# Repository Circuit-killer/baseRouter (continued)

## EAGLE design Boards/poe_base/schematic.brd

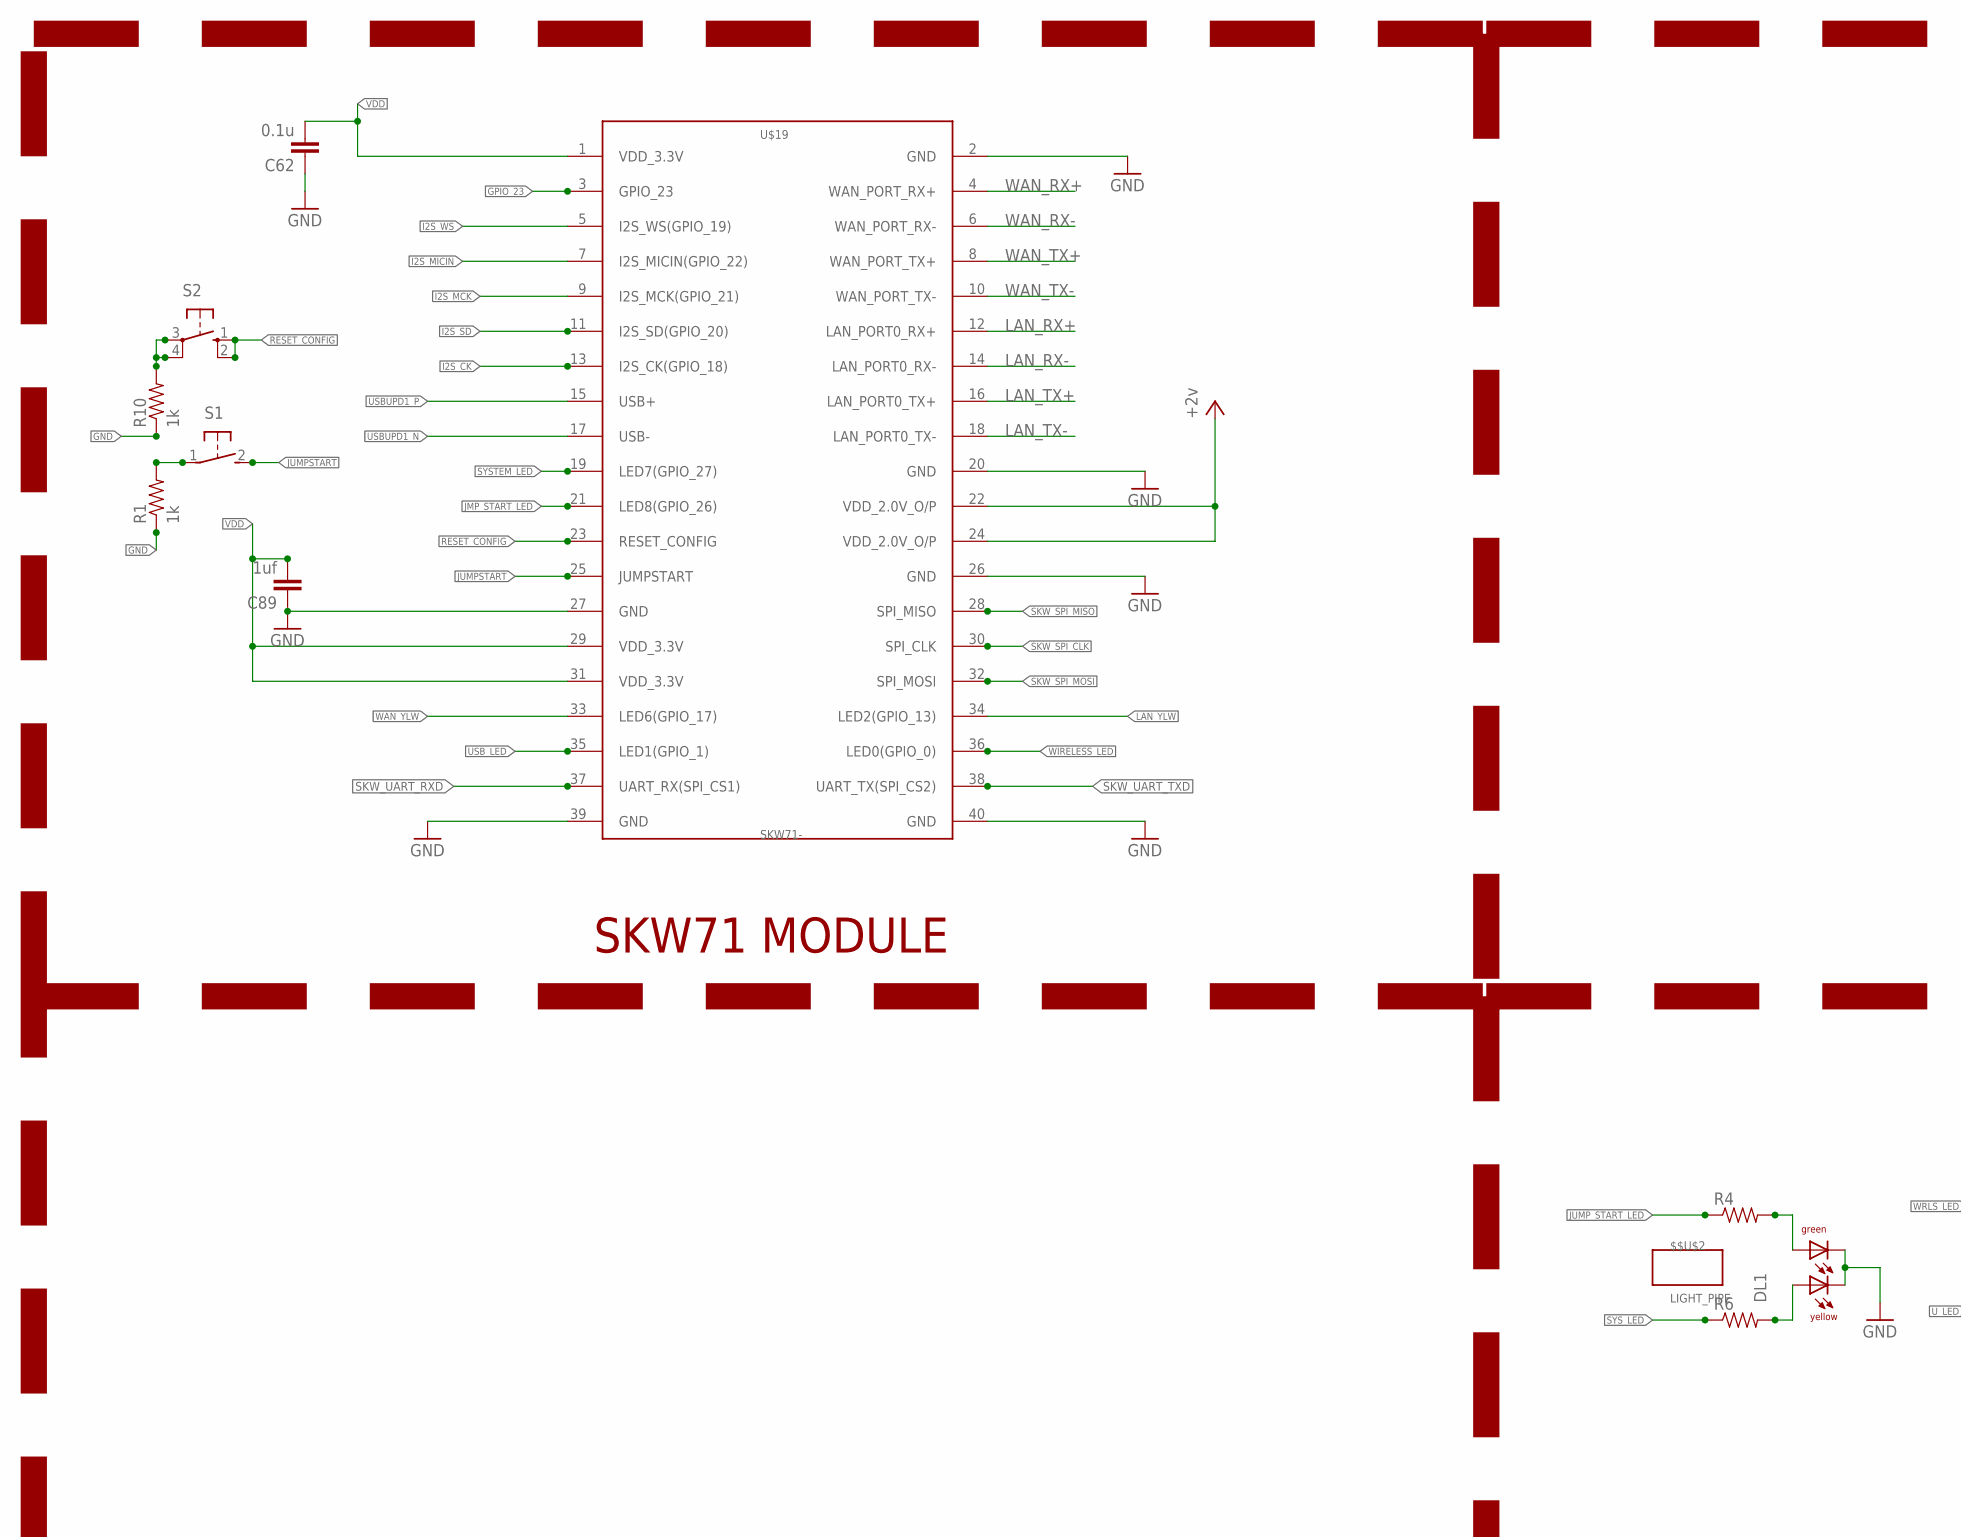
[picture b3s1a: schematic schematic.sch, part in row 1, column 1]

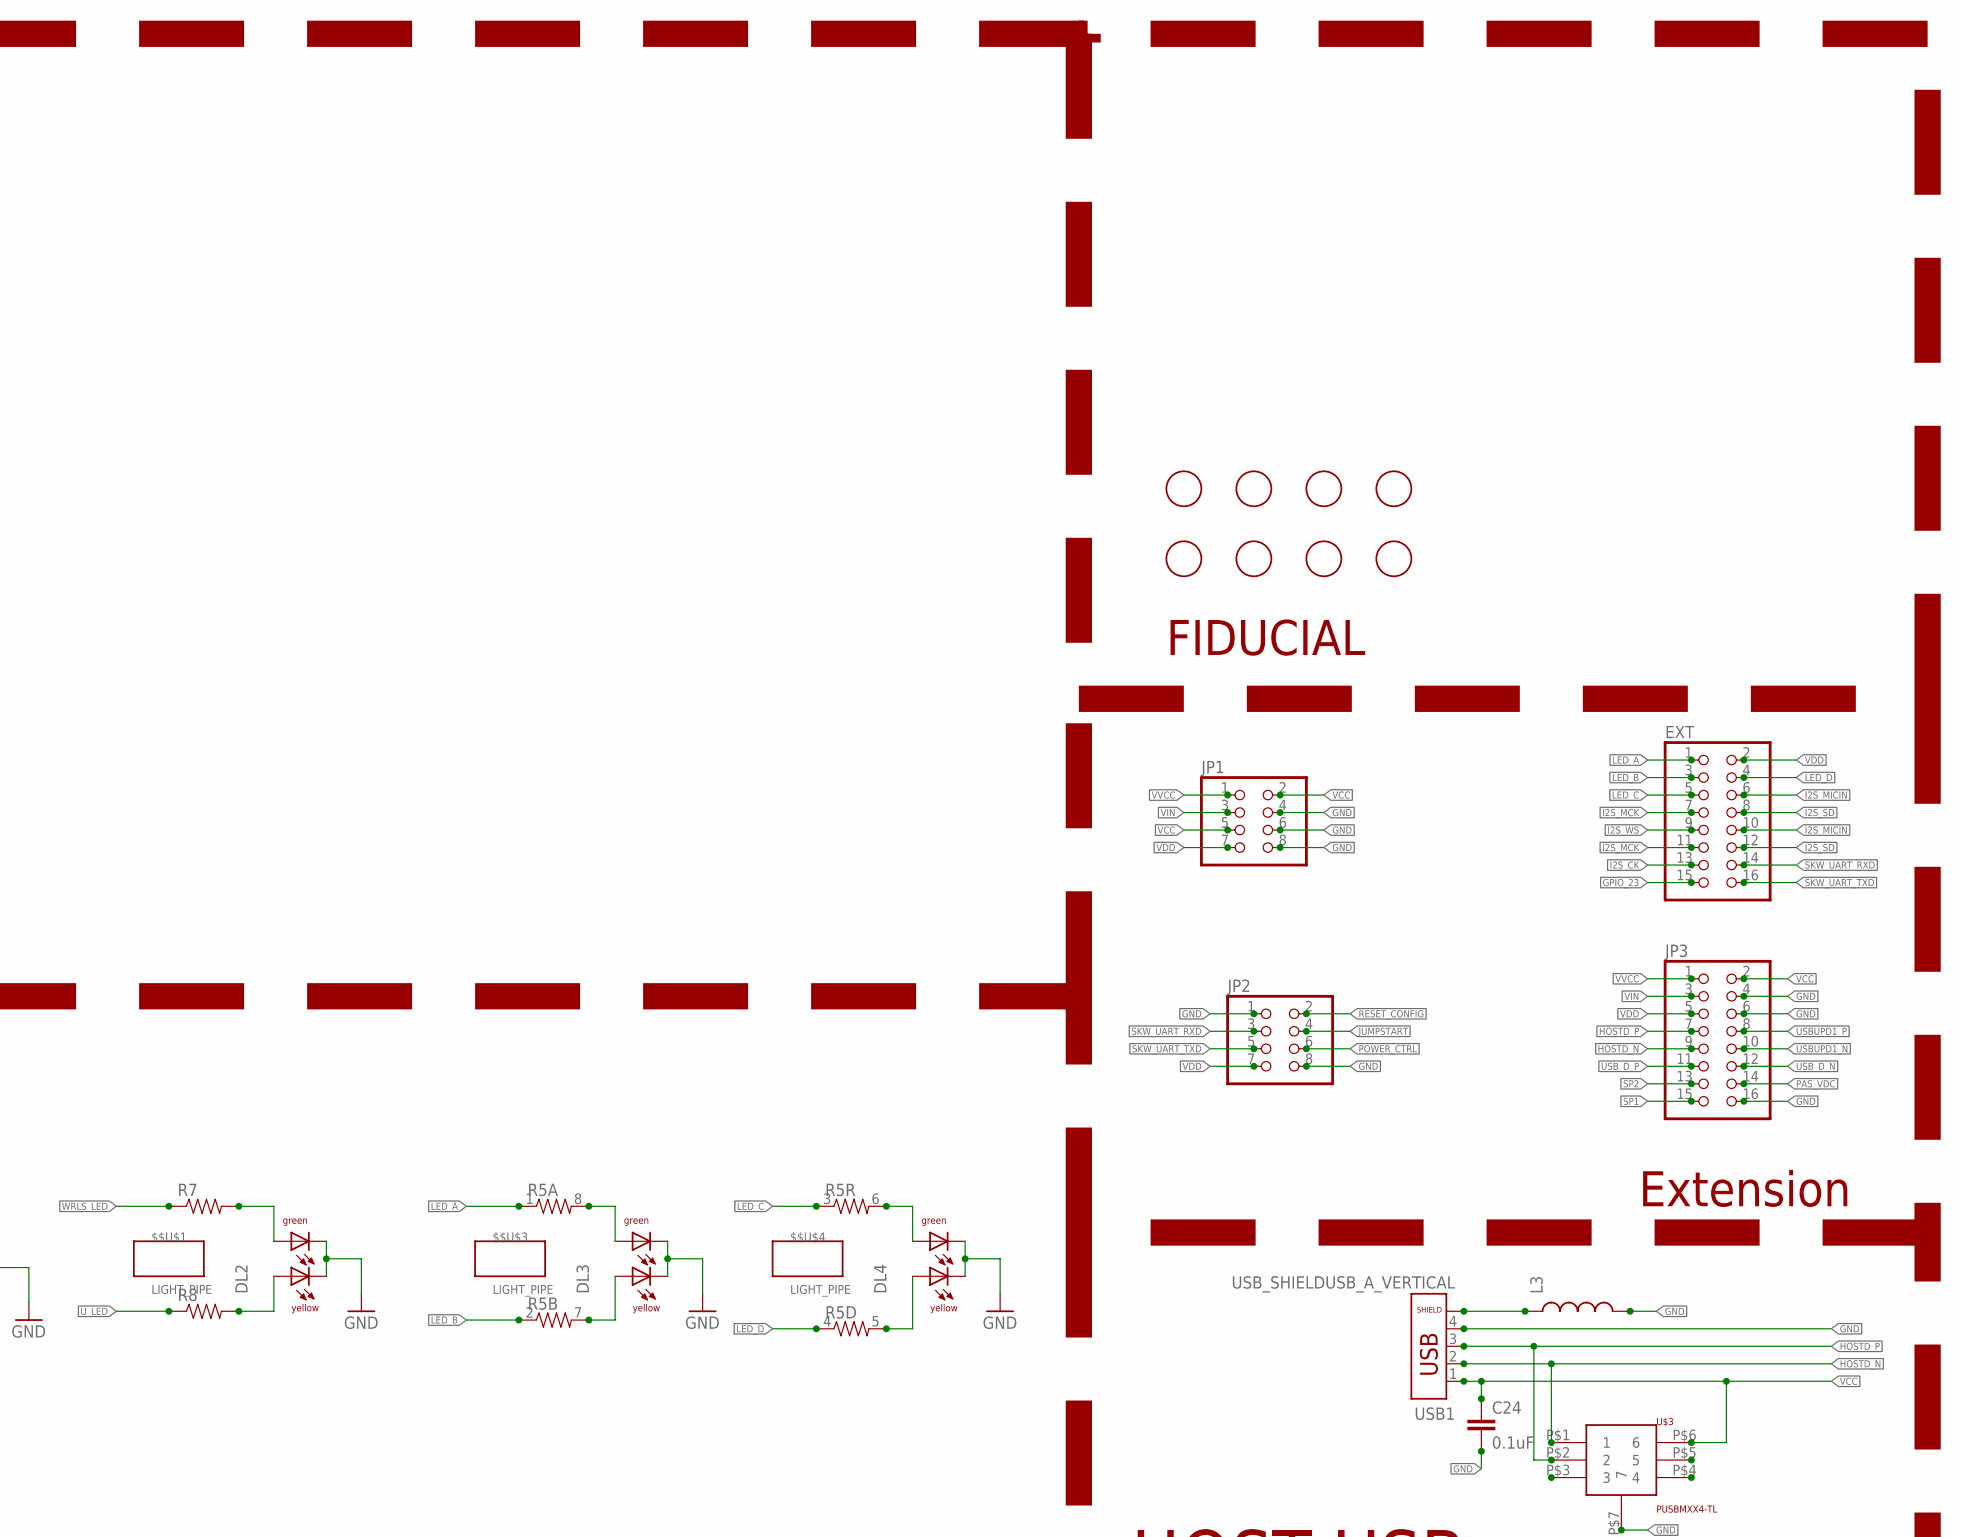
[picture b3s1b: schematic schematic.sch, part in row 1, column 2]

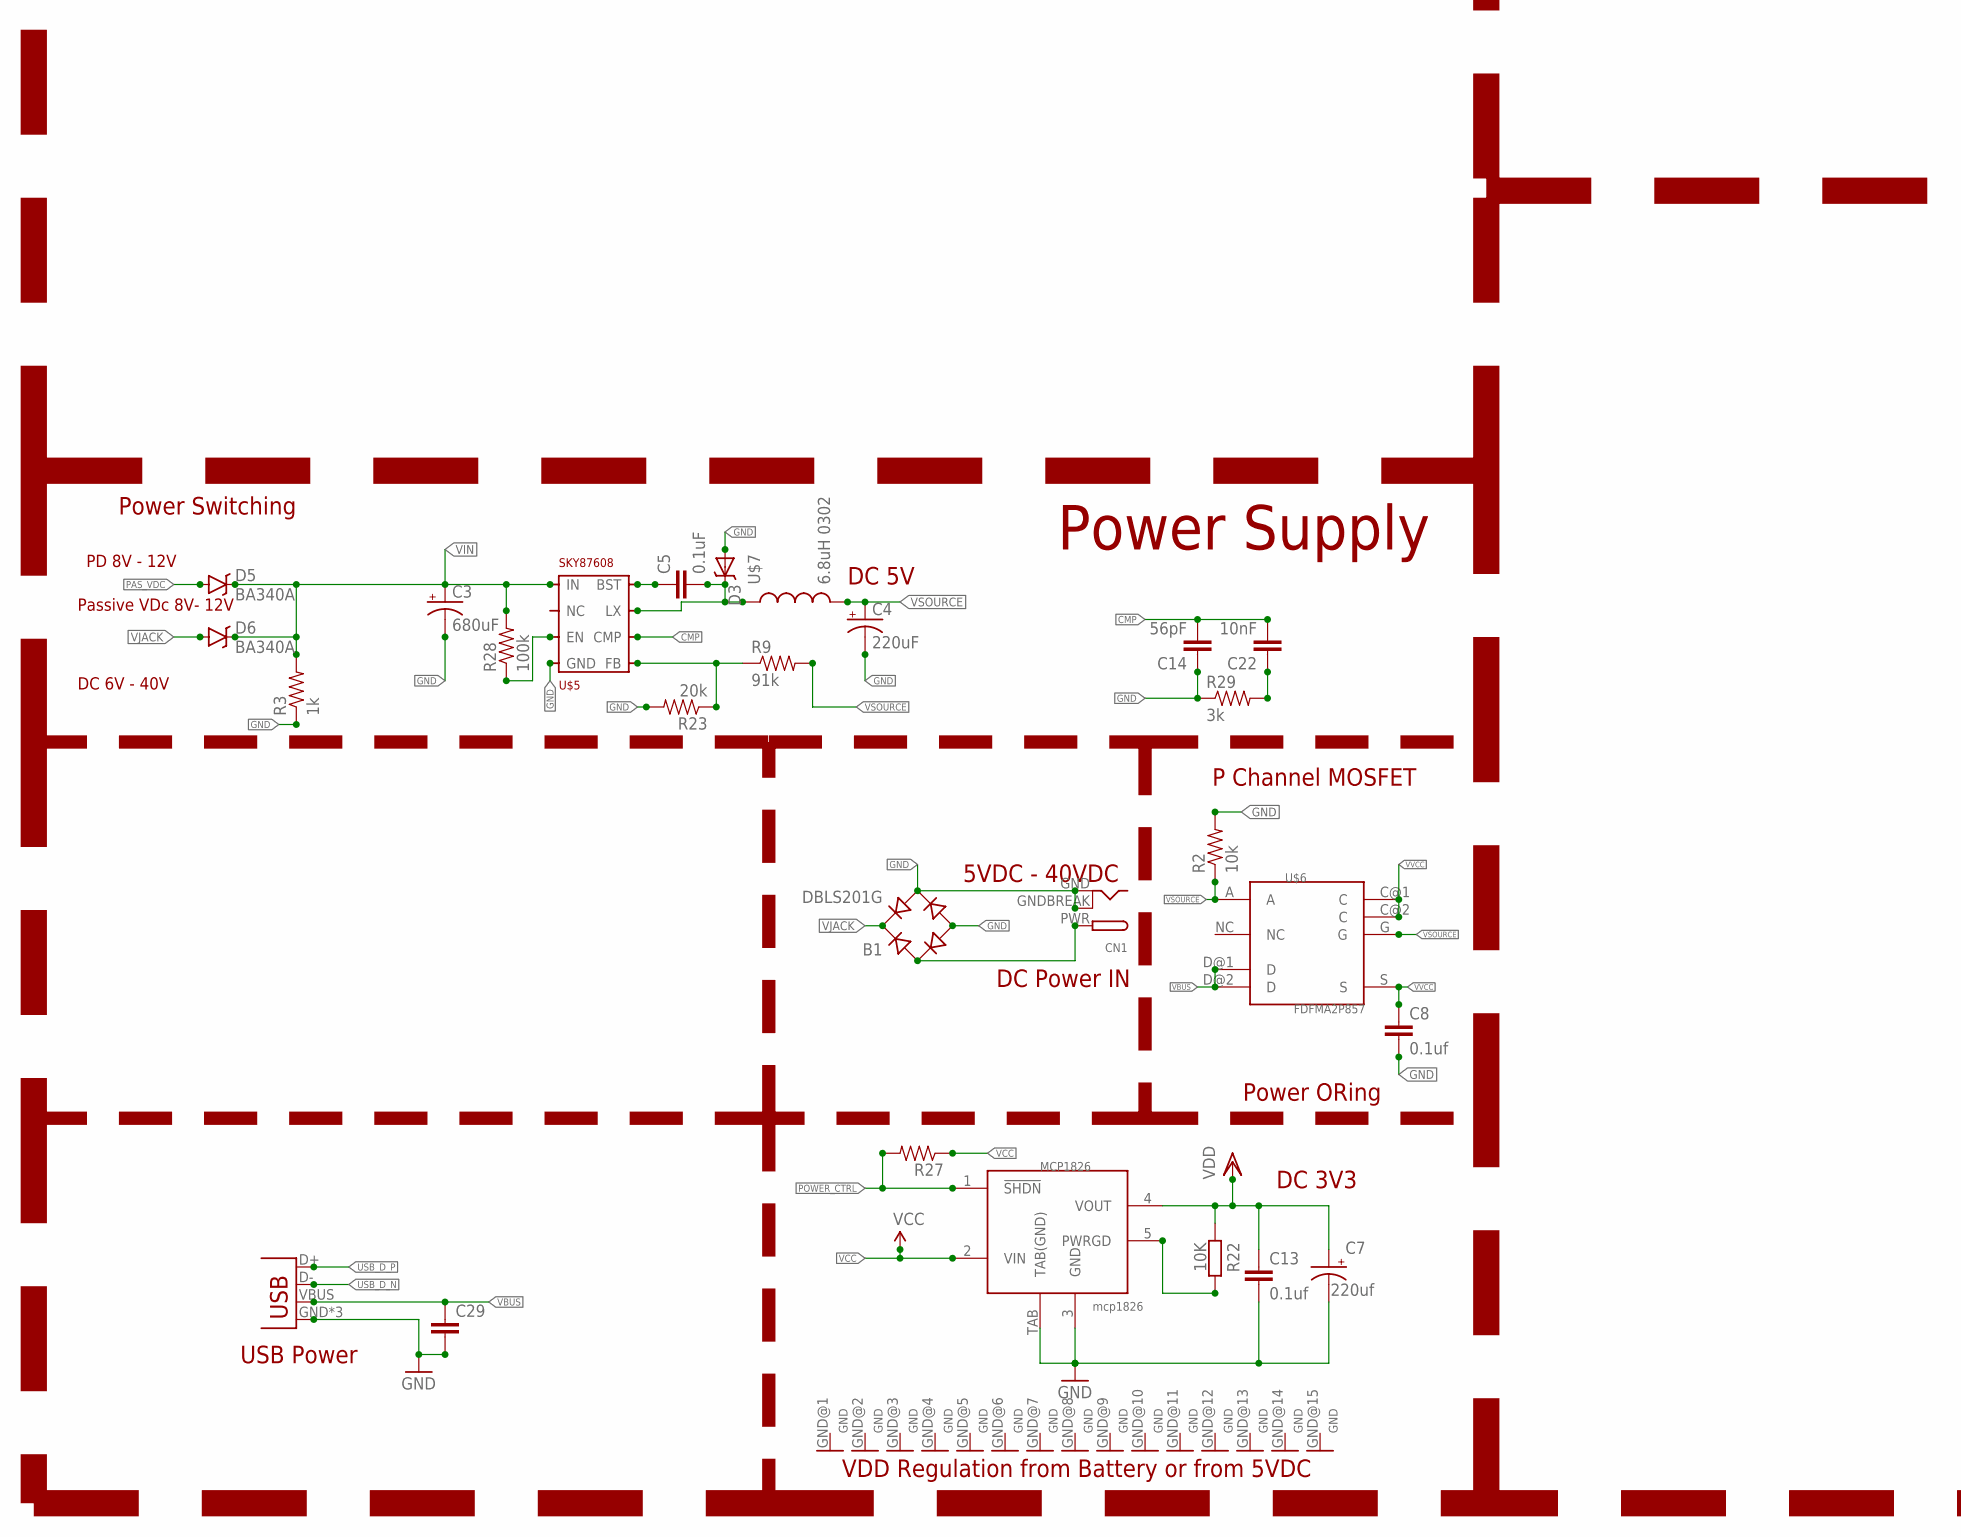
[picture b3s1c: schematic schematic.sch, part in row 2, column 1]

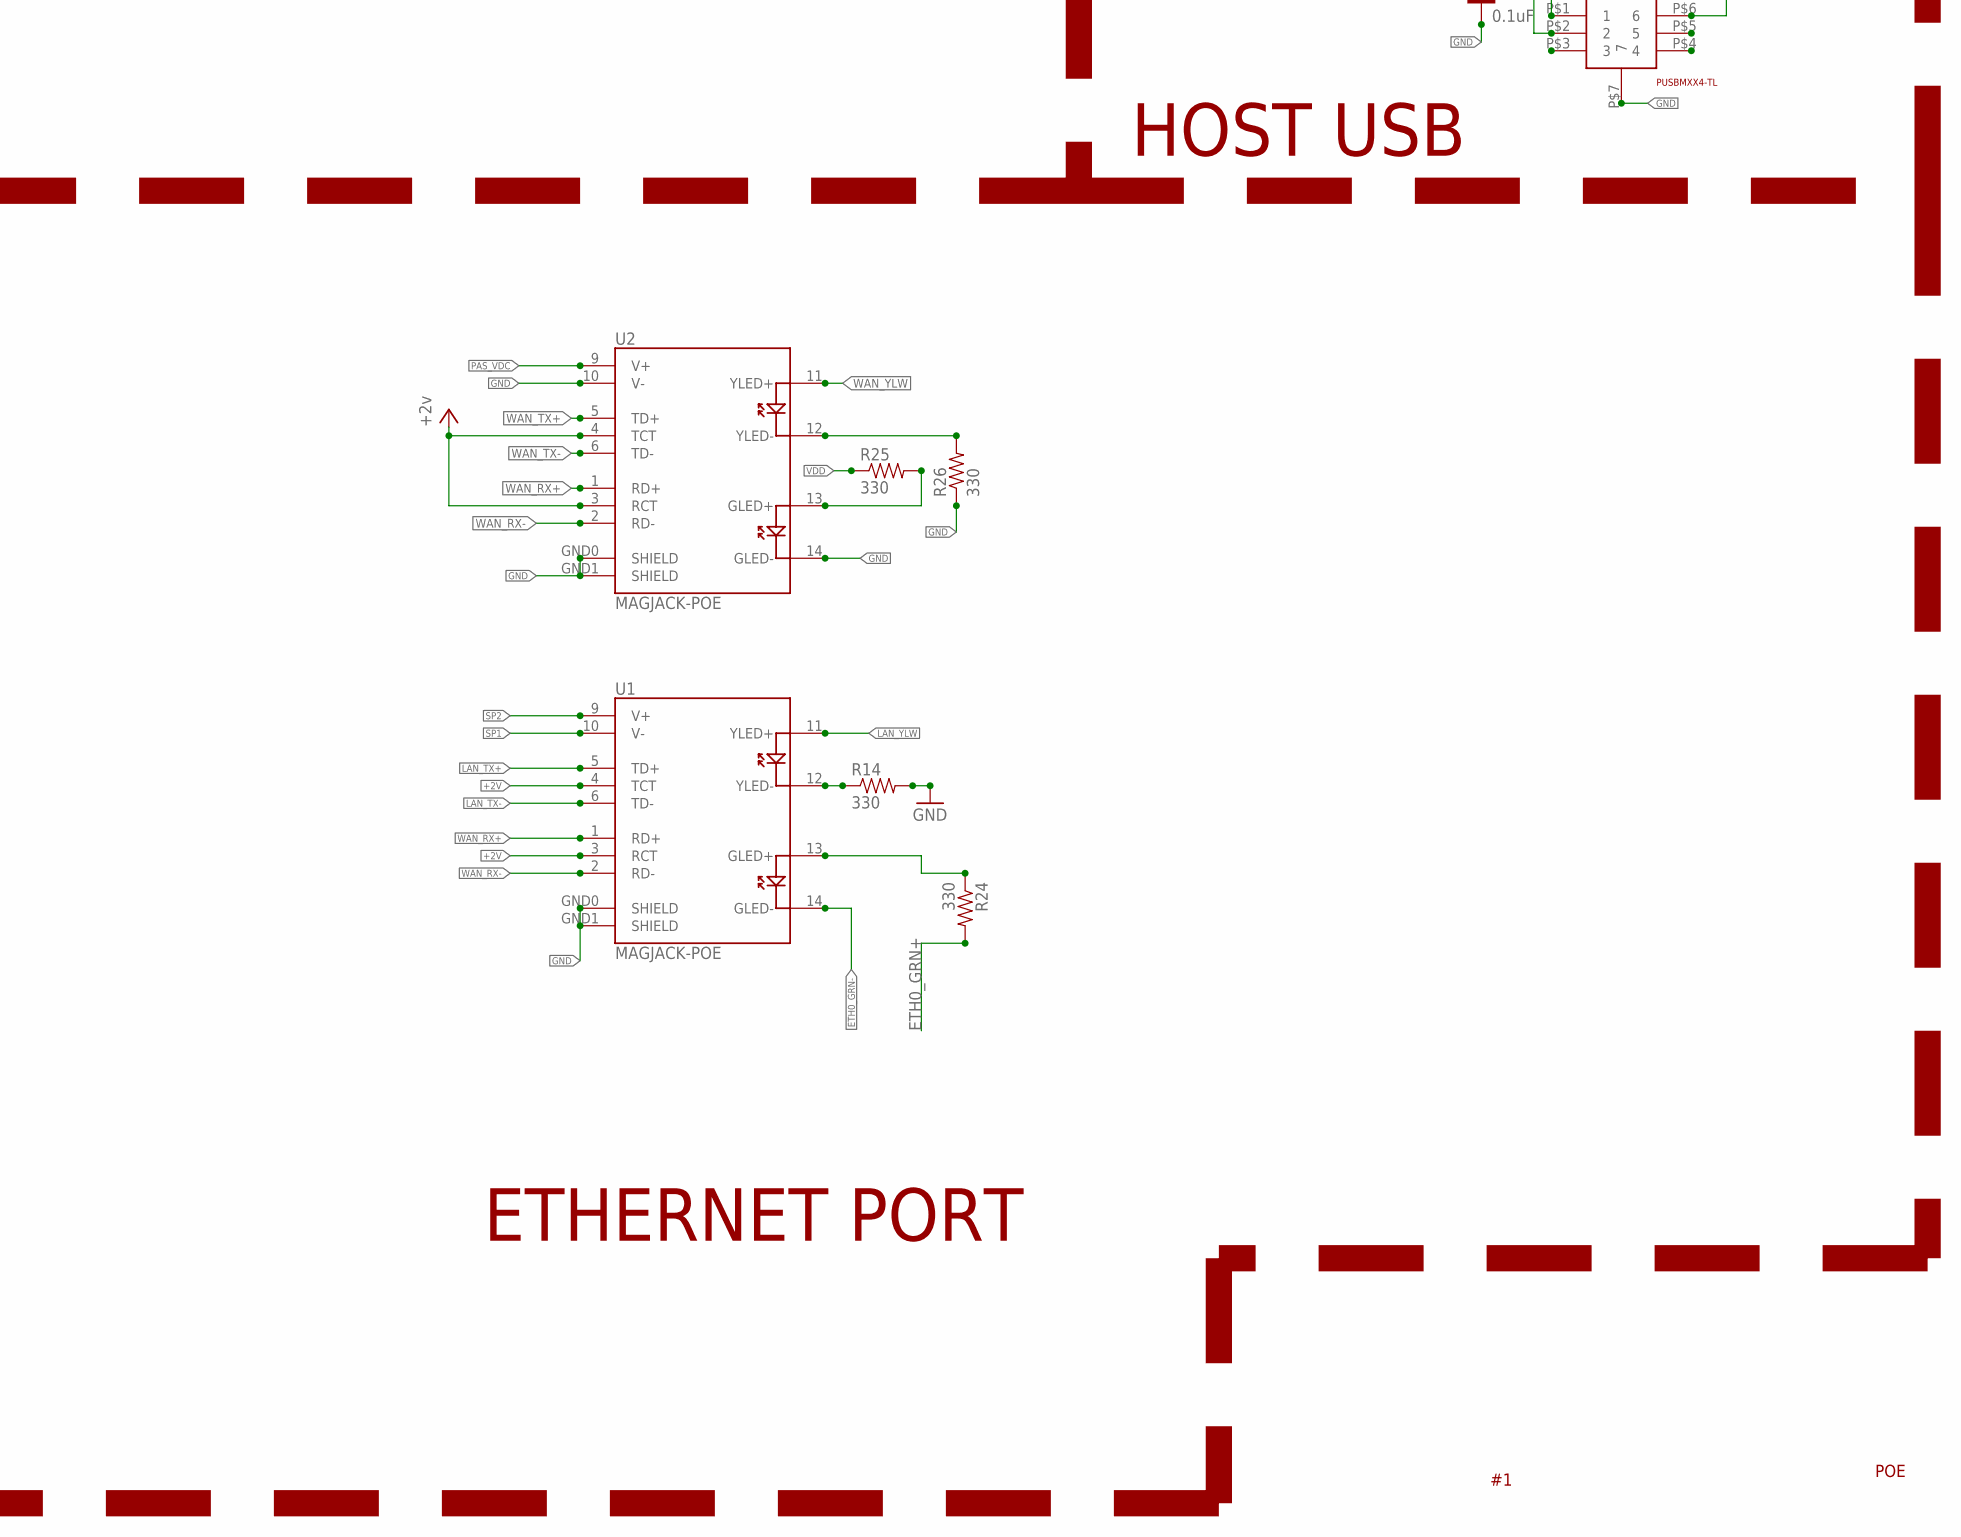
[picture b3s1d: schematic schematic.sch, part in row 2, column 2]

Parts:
$$U$1, $$U$2, $$U$3, $$U$4: LIGHT_PIPE; LIGHT-PIPE
B1: DBLS201G; DBS
C3: 680uF; E3,5-10
C4: 220uF; E5-10,5
C5, C24: 0.1uF; 0402-CAP
C7: 220uf; E5-10,5
C8, C13: 0.1uf; C0402
C14: 56pF; 0402-CAP
C22: 10nF; 0402-CAP
C29: CAP0402-CAP; 0402-CAP
C62: 0.1u; C0603
C89: 1uf; C0603
CN1: DCBARRELPTH; DCJACK_2MM_PTH
D3: DIODE-SCHOTTKY_; SMA-DIODE
D5, D6: BA340A; SMA-DIODE
DL1, DL2, DL3, DL4: DUOLED-1X2; DUOLED-C-0603
EXT: PINHD-2X8; 2X08
JP1, JP2: PINHD-2X4; 2X04
JP3: PINHD-2X8; 2X08
JP4: USB-MICROB
L3: INDUCTOR0402; C0402
MCP1826: mcp1826; SOT223-5
R1, R3, R10: 1k; 0402-RES
R2: 10k; 0402-RES
R4, R6, R7, R8, R27: RESISTOR0402-RES; 0402-RES
R5: RESISTOR-ARRAY0603-ARV; 0603-ARV
R9: 91k; 0402-RES
R14, R24, R25, R26: 330; 0402-RES
R22: 10K; R0402
R23: 20k; 0402-RES
R28: 100k; 0402-RES
R29: 3k; 0402-RES
S1: 31-XX; B3F-31XX
S2: 10-XX; B3F-10XX
U1, U2: MAGJACK-POE
U$3: PUSBMXX4-TL
U$5: SKY87608; 8PIN-SOP-8L-EP
U$6: FDFMA2P857; 6-WDFN-EXPOSED-PAD
U$7: 6.8uH 0302; 0302
U$9, U$11, U$12, U$13, U$14, U$15, U$16, U$17: FIDUCIAL; FIDUCIAL_1MM
U$19: SKW71-; SKW71-SMT
USB1: USB_SHIELDUSB_A_VERTICAL; USB_A_VERTICAL_PTH

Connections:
+2V: U1.3 (RCT), U1.4 (TCT), U2.3 (RCT), U2.4 (TCT), U$19.22 (VDD_2.0V_O/P), U$19.24 (VDD_2.0V_O/P)
CMP: C14.2, C22.2, U$5.P$6 (CMP)
ETH0_GRN+: R24.2
ETH0_GRN-: U1.14 (GLED-)
GND: B1.-, B1.AC2, C3.-, C4.-, C7.-, C8.2, C13.2, C14.1, C24.2, C29.2, C62.1, C89.1, CN1.GND, CN1.GNDBREAK, D3.A, DL1.C1, DL1.C2, DL2.C1, DL2.C2, DL3.C1, DL3.C2, DL4.C1, DL4.C2, JP1.4, JP1.6, JP1.8, JP2.1, JP2.8, JP3.4, JP3.6, JP3.16, JP4.GND, JP4.MT1 (GND), JP4.MT2 (GND), L3.2, MCP1826.3 (GND), MCP1826.GND@1 (GND), MCP1826.GND@2 (GND), MCP1826.GND@3 (GND), MCP1826.GND@4 (GND), MCP1826.GND@5 (GND), MCP1826.GND@6 (GND), MCP1826.GND@7 (GND), MCP1826.GND@8 (GND), MCP1826.GND@9 (GND), MCP1826.GND@10 (GND), MCP1826.GND@11 (GND), MCP1826.GND@12 (GND), MCP1826.GND@13 (GND), MCP1826.GND@14 (GND), MCP1826.GND@15 (GND), MCP1826.TAB (TAB(GND)), R1.1, R2.2, R3.1, R10.1, R14.2, R23.2, R26.1, R29.1, U1.GND0 (SHIELD), U1.GND1 (SHIELD), U2.10 (V-), U2.14 (GLED-), U2.GND0 (SHIELD), U2.GND1 (SHIELD), U$3.P$7 (7), U$5.P$4 (GND), U$19.2 (GND), U$19.20 (GND), U$19.26 (GND), U$19.27 (GND), U$19.39 (GND), U$19.40 (GND), USB1.4
GPIO_23: EXT.15, U$19.3 (GPIO_23)
HOSTD_N: JP3.9, U$3.P$1 (1), USB1.2
HOSTD_P: JP3.7, U$3.P$2 (2), USB1.3
I2S_CK: EXT.13, U$19.13 (I2S_CK(GPIO_18))
I2S_MCK: EXT.7, EXT.11, U$19.9 (I2S_MCK(GPIO_21))
I2S_MICIN: EXT.6, EXT.10, U$19.7 (I2S_MICIN(GPIO_22))
I2S_SD: EXT.8, EXT.12, U$19.11 (I2S_SD(GPIO_20))
I2S_WS: EXT.9, U$19.5 (I2S_WS(GPIO_19))
JMP_START_LED: U$19.21 (LED8(GPIO_26))
JUMPSTART: JP2.4, S1.2 (S), U$19.25 (JUMPSTART)
JUMP_START_LED: R4.1
LAN_RX+: U$19.12 (LAN_PORT0_RX+)
LAN_RX-: U$19.14 (LAN_PORT0_RX-)
LAN_TX+: U1.5 (TD+), U$19.16 (LAN_PORT0_TX+)
LAN_TX-: U1.6 (TD-), U$19.18 (LAN_PORT0_TX-)
LAN_YLW: U1.11 (YLED+), U$19.34 (LED2(GPIO_13))
LED_A: EXT.1, R5.1
LED_B: EXT.3, R5.2 (1)
LED_C: EXT.5, R5.3 (1)
LED_D: EXT.4, R5.4 (1)
unnamed: DL2.A1, R7.2
unnamed: C5.2, D3.C, U$5.P$2 (LX), U$7.P$1 (1)
unnamed: DL1.A1, R4.2
unnamed: DL2.A2, R8.2
unnamed: R10.2, S2.3, S2.4 (P1)
unnamed: R1.2, S1.1
unnamed: DL3.A2, R5.7 (2)
unnamed: DL4.A1, R5.6 (2)
unnamed: MCP1826.5 (PWRGD), R22.2
unnamed: R28.1, U$5.P$7 (EN)
unnamed: R14.1, U1.12 (YLED-)
unnamed: R25.2, U2.13 (GLED+)
unnamed: C5.1, U$5.P$8 (BST)
unnamed: R9.1, R23.1, U$5.P$5 (FB)
unnamed: DL4.A2, R5.5 (2)
unnamed: R26.2, U2.12 (YLED-)
unnamed: DL3.A1, R5.8 (2)
unnamed: C22.1, R29.2
unnamed: DL1.A2, R6.2
unnamed: L3.1, USB1.P$3 (5)
unnamed: B1.AC1, CN1.PWR
unnamed: R24.1, U1.13 (GLED+)
PAS_VDC: D5.A, JP3.14, U2.9 (V+)
POWER_CTRL: JP2.6, MCP1826.1 (!SHDN), R27.2
RESET_CONFIG: JP2.2, S2.1 (S), S2.2 (S1), U$19.23 (RESET_CONFIG)
SKW_SPI_CLK: U$19.30 (SPI_CLK)
SKW_SPI_MISO: U$19.28 (SPI_MISO)
SKW_SPI_MOSI: U$19.32 (SPI_MOSI)
SKW_UART_RXD: EXT.14, JP2.3, U$19.37 (UART_RX(SPI_CS1))
SKW_UART_TXD: EXT.16, JP2.5, U$19.38 (UART_TX(SPI_CS2))
SP1: JP3.15, U1.10 (V-)
SP2: JP3.13, U1.9 (V+)
SYSTEM_LED: U$19.19 (LED7(GPIO_27))
SYS_LED: R6.1
USBUPD1_N: JP3.10, U$19.17 (USB-)
USBUPD1_P: JP3.8, U$19.15 (USB+)
USB_D_N: JP3.12, JP4.D-
USB_D_P: JP3.11, JP4.D+
USB_LED: U$19.35 (LED1(GPIO_1))
U_LED: R8.1
VBUS: C29.1, JP4.VBUS, U$6.D@1 (D), U$6.D@2 (D)
VCC: C24.1, JP1.2, JP1.5, JP3.2, MCP1826.2 (VIN), R27.1, U$3.P$6 (6), USB1.1
VDD: C7.+, C13.1, C62.2, C89.2, EXT.2, JP1.7, JP2.7, JP3.5, MCP1826.4 (VOUT), R22.1, R25.1, U$19.1 (VDD_3.3V), U$19.29 (VDD_3.3V), U$19.31 (VDD_3.3V)
VIN: C3.+, D5.C, D6.C, JP1.3, JP3.3, R3.2, R28.2, U$5.P$1 (IN)
VJACK: B1.+, D6.A
VSOURCE: C4.+, R2.1, R9.2, U$6.A, U$6.G, U$7.P$2 (2)
VVCC: C8.1, JP1.1, JP3.1, U$6.C@1 (C), U$6.C@2 (C), U$6.S
WAN_RX+: U1.1 (RD+), U2.1 (RD+), U$19.4 (WAN_PORT_RX+)
WAN_RX-: U1.2 (RD-), U2.2 (RD-), U$19.6 (WAN_PORT_RX-)
WAN_TX+: U2.5 (TD+), U$19.8 (WAN_PORT_TX+)
WAN_TX-: U2.6 (TD-), U$19.10 (WAN_PORT_TX-)
WAN_YLW: U$19.33 (LED6(GPIO_17))
WIRELESS_LED: U$19.36 (LED0(GPIO_0))
WRLS_LED: R7.1

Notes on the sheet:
SKW71 MODULE
5VDC - 40VDC
PD 8V - 12V
Passive VDc 8V- 12V
Power Switching
USB Power
VDD Regulation from Battery or from 5VDC
DC Power IN
Power Supply
DC 5V
DC 6V - 40V
DC 3V3
Power ORing
P Channel MOSFET
HOST USB
Extension
FIDUCIAL
POE
ETHERNET PORT

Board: 2 copper layers, 69 parts (8 on the bottom side), 63 nets, no tracks yet.
